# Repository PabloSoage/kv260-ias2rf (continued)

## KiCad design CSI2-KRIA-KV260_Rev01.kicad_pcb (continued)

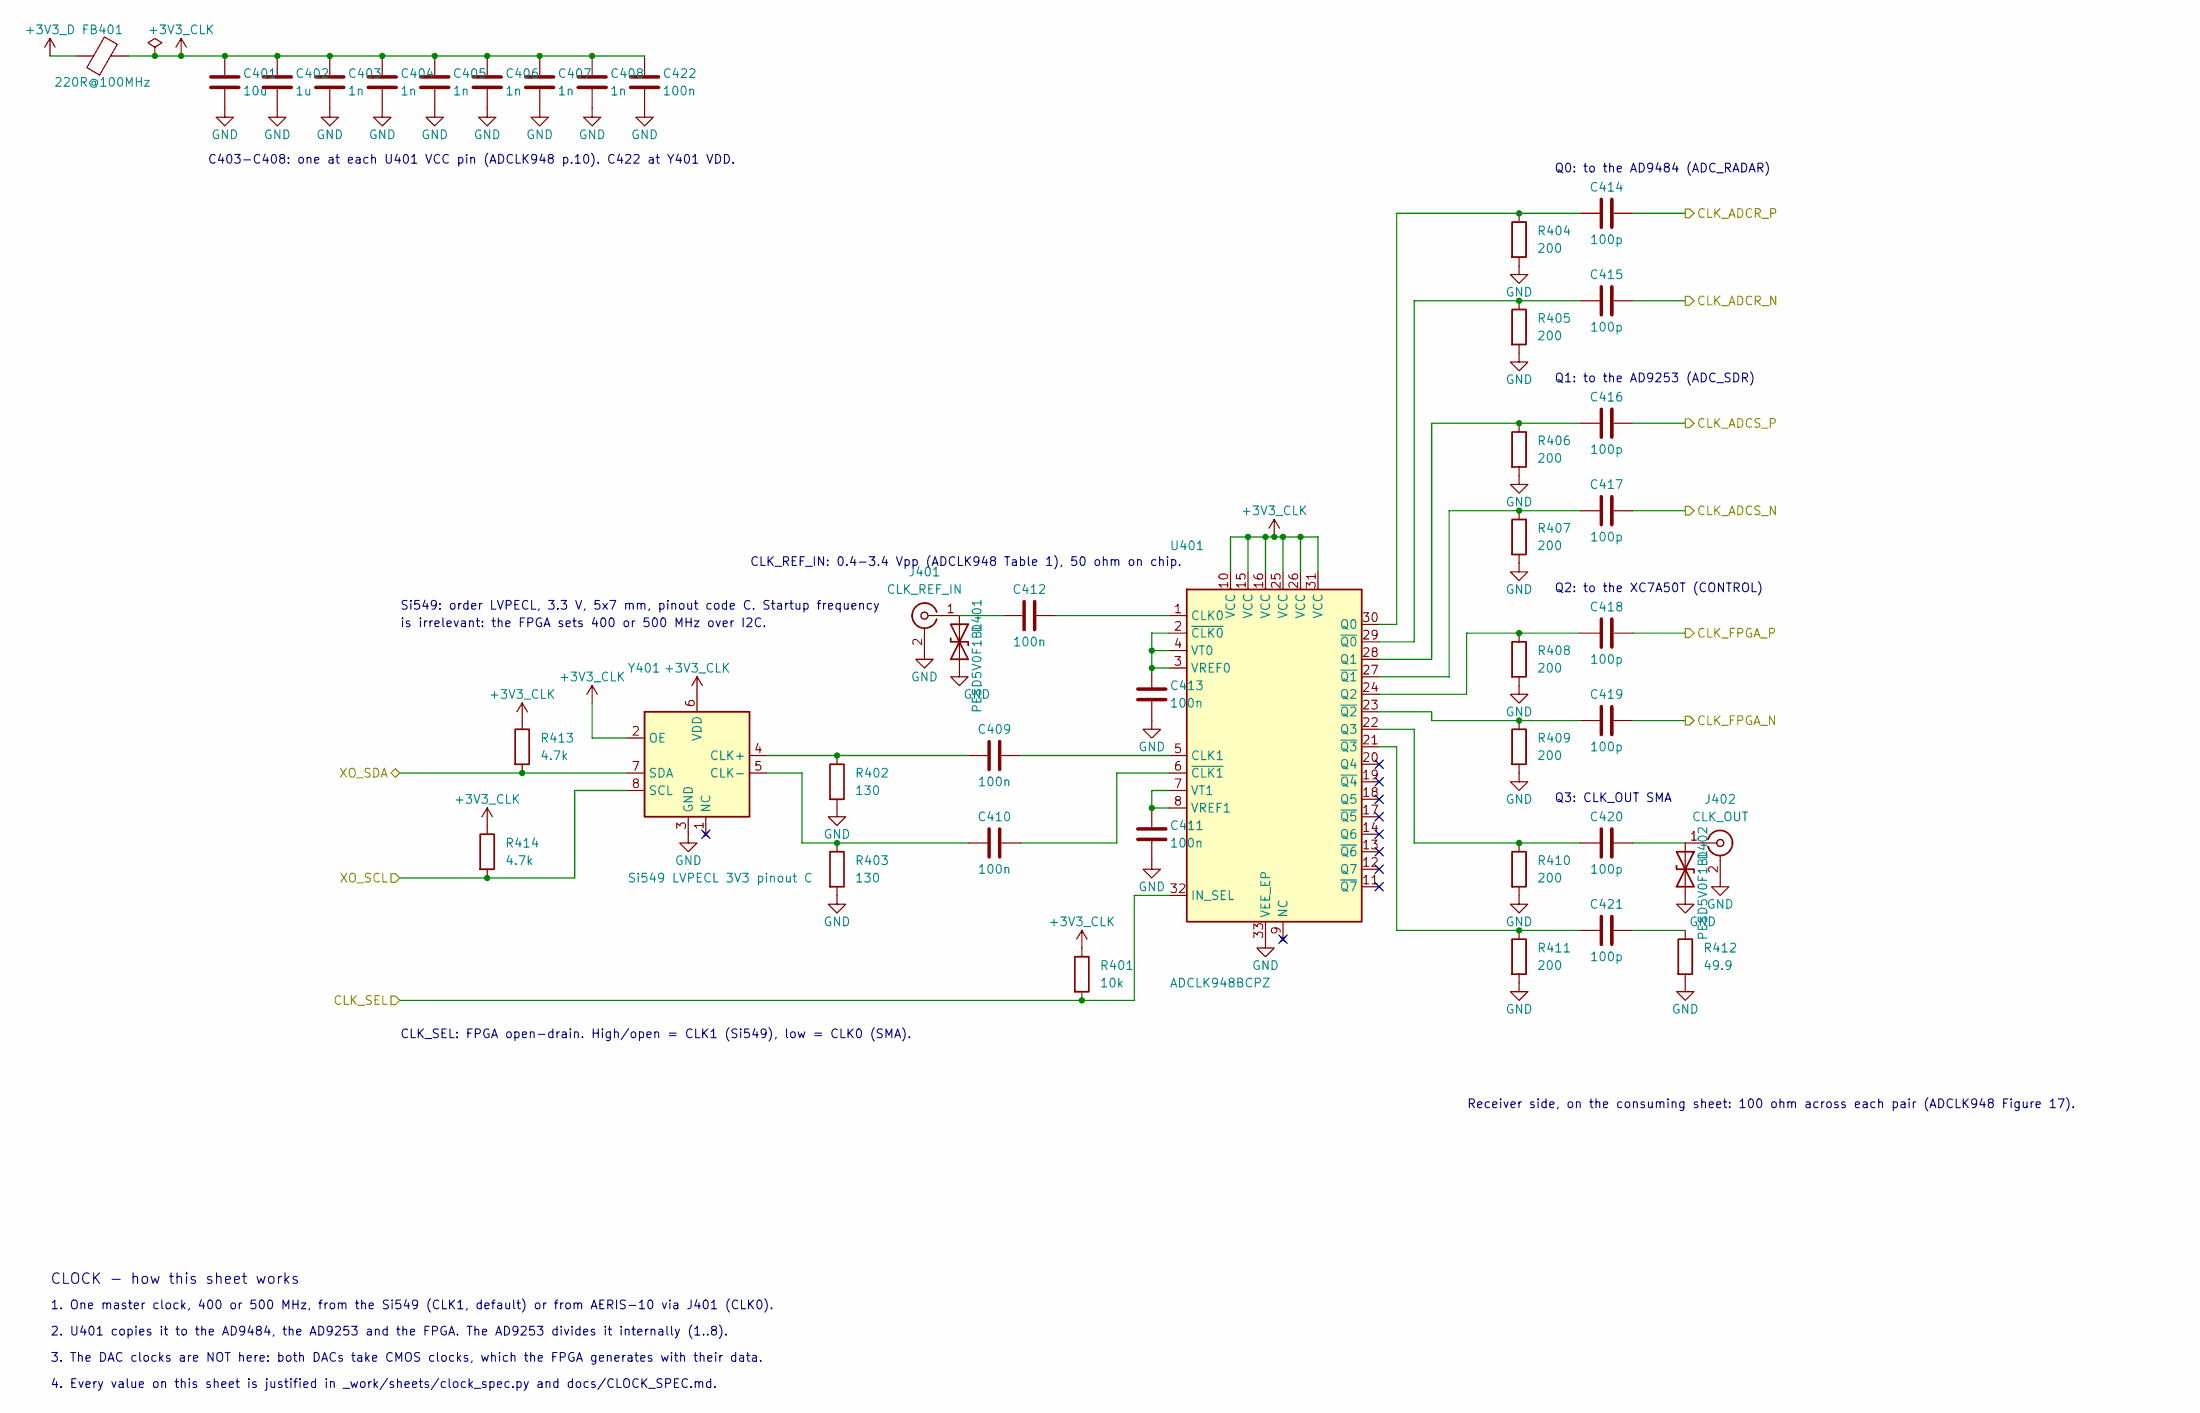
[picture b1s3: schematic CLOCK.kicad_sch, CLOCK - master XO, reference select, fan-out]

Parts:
C401: 10u; C_0805_2012Metric
C402: 1u; C_0402_1005Metric
C403, C404, C405, C406, C407, C408: 1n; C_0402_1005Metric
C409, C410, C411, C412, C413, C422: 100n; C_0402_1005Metric
C414, C415, C416, C417, C418, C419, C420, C421: 100p; C_0402_1005Metric
D401, D402: PESD5V0F1BL; D_SOD-882
FB401: 220R@100MHz; L_0603_1608Metric
J401: CLK_REF_IN; SMA_Samtec_SMA-J-P-H-ST-EM1_EdgeMount
J402: CLK_OUT; SMA_Samtec_SMA-J-P-H-ST-EM1_EdgeMount
R401: 10k; R_0402_1005Metric
R402, R403: 130; R_0402_1005Metric
R404, R405, R406, R407, R408, R409, R410, R411: 200; R_0402_1005Metric
R412: 49.9; R_0402_1005Metric
R413, R414: 4.7k; R_0402_1005Metric
U401: ADCLK948BCPZ; LFCSP-32-1EP_5x5mm_P0.5mm_EP2.7x2.7mm
Y401: Si549 LVPECL 3V3 pinout C; Oscillator_SMD_SI570_SI571_Standard

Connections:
+3V3_CLK: C401.1, C402.1, C403.1, C404.1, C405.1, C406.1, C407.1, C408.1, C422.1, FB401.2, R401.1, R413.1, R414.1, U401.10 (VCC), U401.15 (VCC), U401.16 (VCC), U401.25 (VCC), U401.26 (VCC), U401.31 (VCC), Y401.2 (OE), Y401.6 (VDD); also elsewhere on the board
+3V3_D: FB401.1; also elsewhere on the board
/CLK_ADCR_N: C415.2; also elsewhere on the board
/CLK_ADCR_P: C414.2; also elsewhere on the board
/CLK_ADCS_N: C417.2; also elsewhere on the board
/CLK_ADCS_P: C416.2; also elsewhere on the board
/CLK_FPGA_N: C419.2; also elsewhere on the board
/CLK_FPGA_P: C418.2; also elsewhere on the board
/CLK_SEL: R401.2, U401.32 (IN_SEL); also elsewhere on the board
/XO_SCL: R414.2, Y401.8 (SCL); also elsewhere on the board
/XO_SDA: R413.2, Y401.7 (SDA); also elsewhere on the board
GND: C401.2, C402.2, C403.2, C404.2, C405.2, C406.2, C407.2, C408.2, C411.2, C413.2, C422.2, D401.2 (A2), D402.2 (A2), J401.2 (Ext), J402.2 (Ext), R402.2, R403.2, R404.2, R405.2, R406.2, R407.2, R408.2, R409.2, R410.2, R411.2, R412.2, U401.33 (VEE_EP), Y401.3 (GND); also elsewhere on the board
unnamed: C421.2, R412.1
unnamed: C412.1, D401.1 (A1), J401.1 (In)
unnamed: C420.2, D402.1 (A1), J402.1 (In)
unnamed: C412.2, U401.1 (CLK0)
unnamed: C409.2, U401.5 (CLK1)
unnamed: C414.1, R404.1, U401.30 (Q0)
unnamed: C416.1, R406.1, U401.28 (Q1)
unnamed: C418.1, R408.1, U401.24 (Q2)
unnamed: C420.1, R410.1, U401.22 (Q3)
unnamed: C413.1, U401.2 (~CLK0), U401.3 (VREF0), U401.4 (VT0)
unnamed: C411.1, U401.7 (VT1), U401.8 (VREF1)
unnamed: C410.2, U401.6 (~CLK1)
unnamed: C415.1, R405.1, U401.29 (~Q0)
unnamed: C417.1, R407.1, U401.27 (~Q1)
unnamed: C419.1, R409.1, U401.23 (~Q2)
unnamed: C421.1, R411.1, U401.21 (~Q3)
unnamed: C409.1, R402.1, Y401.4 (CLK+)
unnamed: C410.1, R403.1, Y401.5 (CLK-)

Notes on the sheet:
C403-C408: one at each U401 VCC pin (ADCLK948 p.10). C422 at Y401 VDD.
CLK_REF_IN: 0.4-3.4 Vpp (ADCLK948 Table 1), 50 ohm on chip.
Si549: order LVPECL, 3.3 V, 5x7 mm, pinout code C. Startup frequency
is irrelevant: the FPGA sets 400 or 500 MHz over I2C.
CLK_SEL: FPGA open-drain. High/open = CLK1 (Si549), low = CLK0 (SMA).
Q0: to the AD9484 (ADC_RADAR)
Q1: to the AD9253 (ADC_SDR)
Q2: to the XC7A50T (CONTROL)
Q3: CLK_OUT SMA
Receiver side, on the consuming sheet: 100 ohm across each pair (ADCLK948 Figure 17).
CLOCK - how this sheet works
1. One master clock, 400 or 500 MHz, from the Si549 (CLK1, default) or from AERIS-10 via J401 (CLK0).
2. U401 copies it to the AD9484, the AD9253 and the FPGA. The AD9253 divides it internally (1..8).
3. The DAC clocks are NOT here: both DACs take CMOS clocks, which the FPGA generates with their data.
4. Every value on this sheet is justified in _work/sheets/clock_spec.py and docs/CLOCK_SPEC.md.

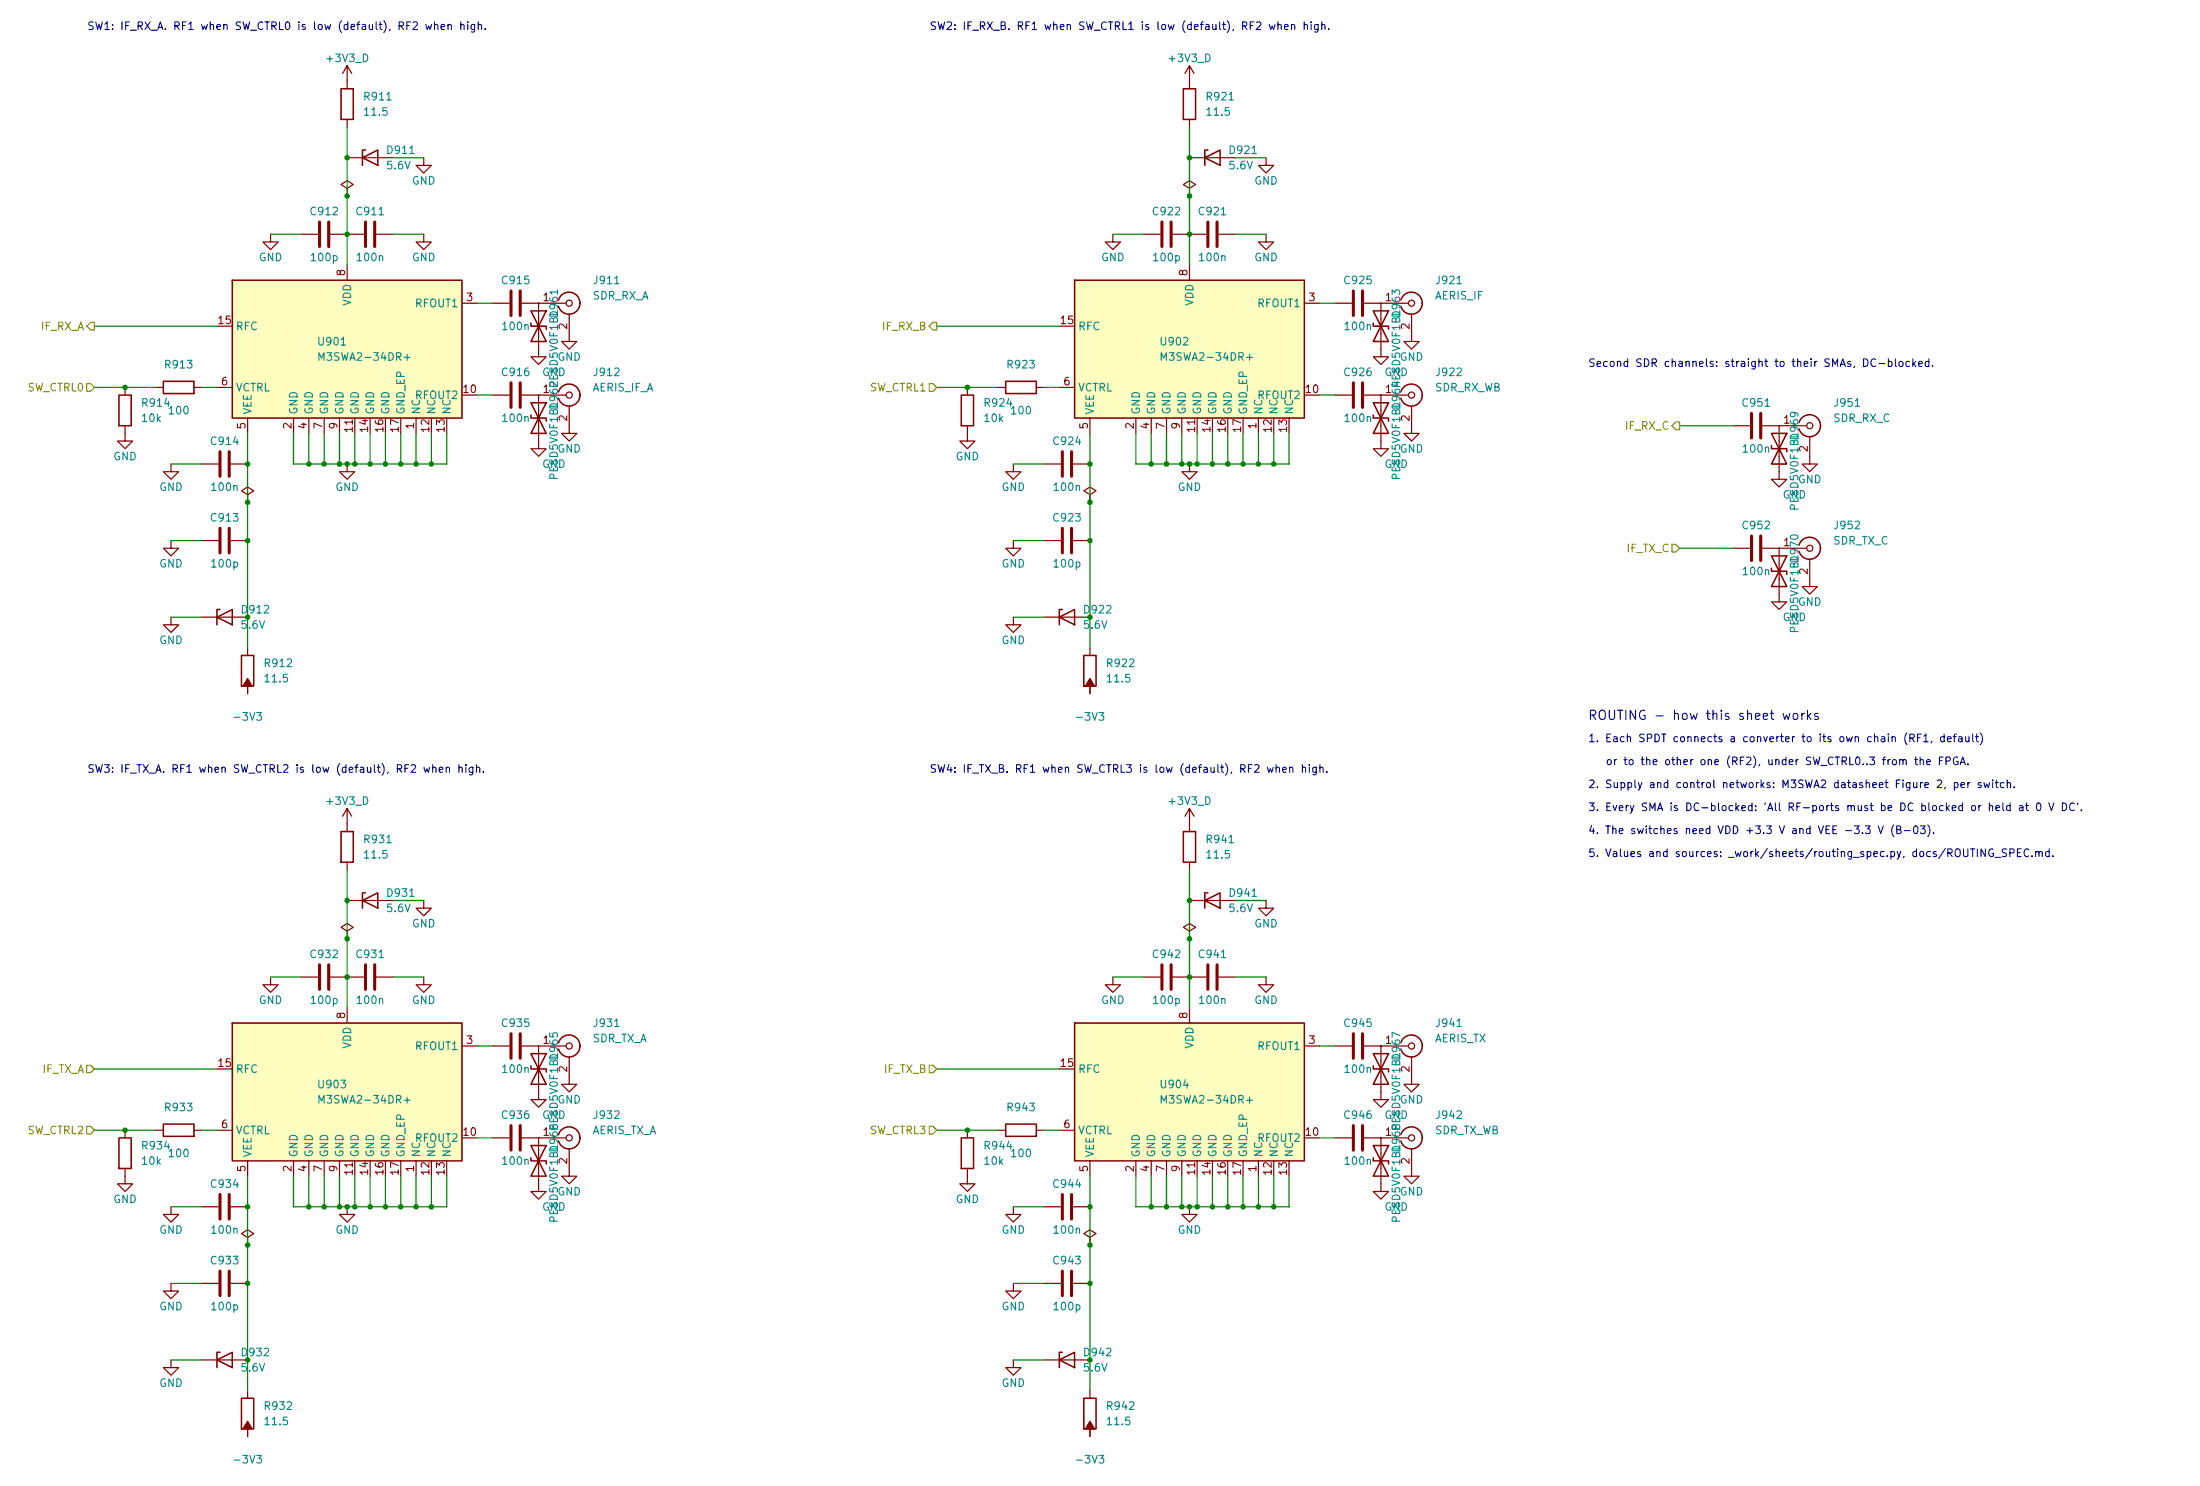
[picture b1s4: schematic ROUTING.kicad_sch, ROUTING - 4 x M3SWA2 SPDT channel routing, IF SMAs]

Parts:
C911, C914, C915, C916, C921, C924, C925, C926, C931, C934, C935, C936, C941, C944, C945, C946, C951, C952: 100n; C_0402_1005Metric
C912, C913, C922, C923, C932, C933, C942, C943: 100p; C_0402_1005Metric
D911, D912, D921, D922, D931, D932, D941, D942: 5.6V; D_SOD-123
D961, D962, D963, D964, D965, D966, D967, D968, D969, D970: PESD5V0F1BL; D_SOD-882
J911: SDR_RX_A; SMA_Samtec_SMA-J-P-H-ST-EM1_EdgeMount
J912: AERIS_IF_A; SMA_Samtec_SMA-J-P-H-ST-EM1_EdgeMount
J921: AERIS_IF; SMA_Samtec_SMA-J-P-H-ST-EM1_EdgeMount
J922: SDR_RX_WB; SMA_Samtec_SMA-J-P-H-ST-EM1_EdgeMount
J931: SDR_TX_A; SMA_Samtec_SMA-J-P-H-ST-EM1_EdgeMount
J932: AERIS_TX_A; SMA_Samtec_SMA-J-P-H-ST-EM1_EdgeMount
J941: AERIS_TX; SMA_Samtec_SMA-J-P-H-ST-EM1_EdgeMount
J942: SDR_TX_WB; SMA_Samtec_SMA-J-P-H-ST-EM1_EdgeMount
J951: SDR_RX_C; SMA_Samtec_SMA-J-P-H-ST-EM1_EdgeMount
J952: SDR_TX_C; SMA_Samtec_SMA-J-P-H-ST-EM1_EdgeMount
R911, R912, R921, R922, R931, R932, R941, R942: 11.5; R_0402_1005Metric
R913, R923, R933, R943: 100; R_0402_1005Metric
R914, R924, R934, R944: 10k; R_0402_1005Metric
U901, U902, U903, U904: M3SWA2-34DR+; MiniCircuits_DQ3005

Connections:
+3V3_D: R911.1, R921.1, R931.1, R941.1; also elsewhere on the board
-3V3: R912.2, R922.2, R932.2, R942.2; also elsewhere on the board
/IF_RX_A: U901.15 (RFC); also elsewhere on the board
/IF_RX_B: U902.15 (RFC); also elsewhere on the board
/IF_RX_C: C951.1; also elsewhere on the board
/IF_TX_A: U903.15 (RFC); also elsewhere on the board
/IF_TX_B: U904.15 (RFC); also elsewhere on the board
/IF_TX_C: C952.1; also elsewhere on the board
/SW_CTRL0: R913.1, R914.1; also elsewhere on the board
/SW_CTRL1: R923.1, R924.1; also elsewhere on the board
/SW_CTRL2: R933.1, R934.1; also elsewhere on the board
/SW_CTRL3: R943.1, R944.1; also elsewhere on the board
GND: C911.2, C912.2, C913.1, C914.1, C921.2, C922.2, C923.1, C924.1, C931.2, C932.2, C933.1, C934.1, C941.2, C942.2, C943.1, C944.1, D911.2 (A), D912.1 (K), D921.2 (A), D922.1 (K), D931.2 (A), D932.1 (K), D941.2 (A), D942.1 (K), D961.2 (A2), D962.2 (A2), D963.2 (A2), D964.2 (A2), D965.2 (A2), D966.2 (A2), D967.2 (A2), D968.2 (A2), D969.2 (A2), D970.2 (A2), J911.2 (Ext), J912.2 (Ext), J921.2 (Ext), J922.2 (Ext), J931.2 (Ext), J932.2 (Ext), J941.2 (Ext), J942.2 (Ext), J951.2 (Ext), J952.2 (Ext), R914.2, R924.2, R934.2, R944.2, U901.1 (NC), U901.2 (GND), U901.4 (GND), U901.7 (GND), U901.9 (GND), U901.11 (GND), U901.12 (NC), U901.13 (NC), U901.14 (GND), U901.16 (GND), U901.17 (GND_EP), U902.1 (NC), U902.2 (GND), U902.4 (GND), U902.7 (GND), U902.9 (GND), U902.11 (GND), U902.12 (NC), U902.13 (NC), U902.14 (GND), U902.16 (GND), U902.17 (GND_EP), U903.1 (NC), U903.2 (GND), U903.4 (GND), U903.7 (GND), U903.9 (GND), U903.11 (GND), U903.12 (NC), U903.13 (NC), U903.14 (GND), U903.16 (GND), U903.17 (GND_EP), U904.1 (NC), U904.2 (GND), U904.4 (GND), U904.7 (GND), U904.9 (GND), U904.11 (GND), U904.12 (NC), U904.13 (NC), U904.14 (GND), U904.16 (GND), U904.17 (GND_EP); also elsewhere on the board
unnamed: C911.1, C912.1, D911.1 (K), R911.2, U901.8 (VDD)
unnamed: C913.2, C914.2, D912.2 (A), R912.1, U901.5 (VEE)
unnamed: C921.1, C922.1, D921.1 (K), R921.2, U902.8 (VDD)
unnamed: C923.2, C924.2, D922.2 (A), R922.1, U902.5 (VEE)
unnamed: C931.1, C932.1, D931.1 (K), R931.2, U903.8 (VDD)
unnamed: C933.2, C934.2, D932.2 (A), R932.1, U903.5 (VEE)
unnamed: C941.1, C942.1, D941.1 (K), R941.2, U904.8 (VDD)
unnamed: C943.2, C944.2, D942.2 (A), R942.1, U904.5 (VEE)
unnamed: C915.2, D961.1 (A1), J911.1 (In)
unnamed: C916.2, D962.1 (A1), J912.1 (In)
unnamed: C925.2, D963.1 (A1), J921.1 (In)
unnamed: C926.2, D964.1 (A1), J922.1 (In)
unnamed: C935.2, D965.1 (A1), J931.1 (In)
unnamed: C936.2, D966.1 (A1), J932.1 (In)
unnamed: C945.2, D967.1 (A1), J941.1 (In)
unnamed: C946.2, D968.1 (A1), J942.1 (In)
unnamed: C951.2, D969.1 (A1), J951.1 (In)
unnamed: C952.2, D970.1 (A1), J952.1 (In)
unnamed: C915.1, U901.3 (RFOUT1)
unnamed: C916.1, U901.10 (RFOUT2)
unnamed: R913.2, U901.6 (VCTRL)
unnamed: C925.1, U902.3 (RFOUT1)
unnamed: C926.1, U902.10 (RFOUT2)
unnamed: R923.2, U902.6 (VCTRL)
unnamed: C935.1, U903.3 (RFOUT1)
unnamed: C936.1, U903.10 (RFOUT2)
unnamed: R933.2, U903.6 (VCTRL)
unnamed: C945.1, U904.3 (RFOUT1)
unnamed: C946.1, U904.10 (RFOUT2)
unnamed: R943.2, U904.6 (VCTRL)

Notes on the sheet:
SW1: IF_RX_A. RF1 when SW_CTRL0 is low (default), RF2 when high.
SW2: IF_RX_B. RF1 when SW_CTRL1 is low (default), RF2 when high.
SW3: IF_TX_A. RF1 when SW_CTRL2 is low (default), RF2 when high.
SW4: IF_TX_B. RF1 when SW_CTRL3 is low (default), RF2 when high.
Second SDR channels: straight to their SMAs, DC-blocked.
ROUTING - how this sheet works
1. Each SPDT connects a converter to its own chain (RF1, default)
or to the other one (RF2), under SW_CTRL0..3 from the FPGA.
2. Supply and control networks: M3SWA2 datasheet Figure 2, per switch.
3. Every SMA is DC-blocked: 'All RF-ports must be DC blocked or held at 0 V DC'.
4. The switches need VDD +3.3 V and VEE -3.3 V (B-03).
5. Values and sources: _work/sheets/routing_spec.py, docs/ROUTING_SPEC.md.

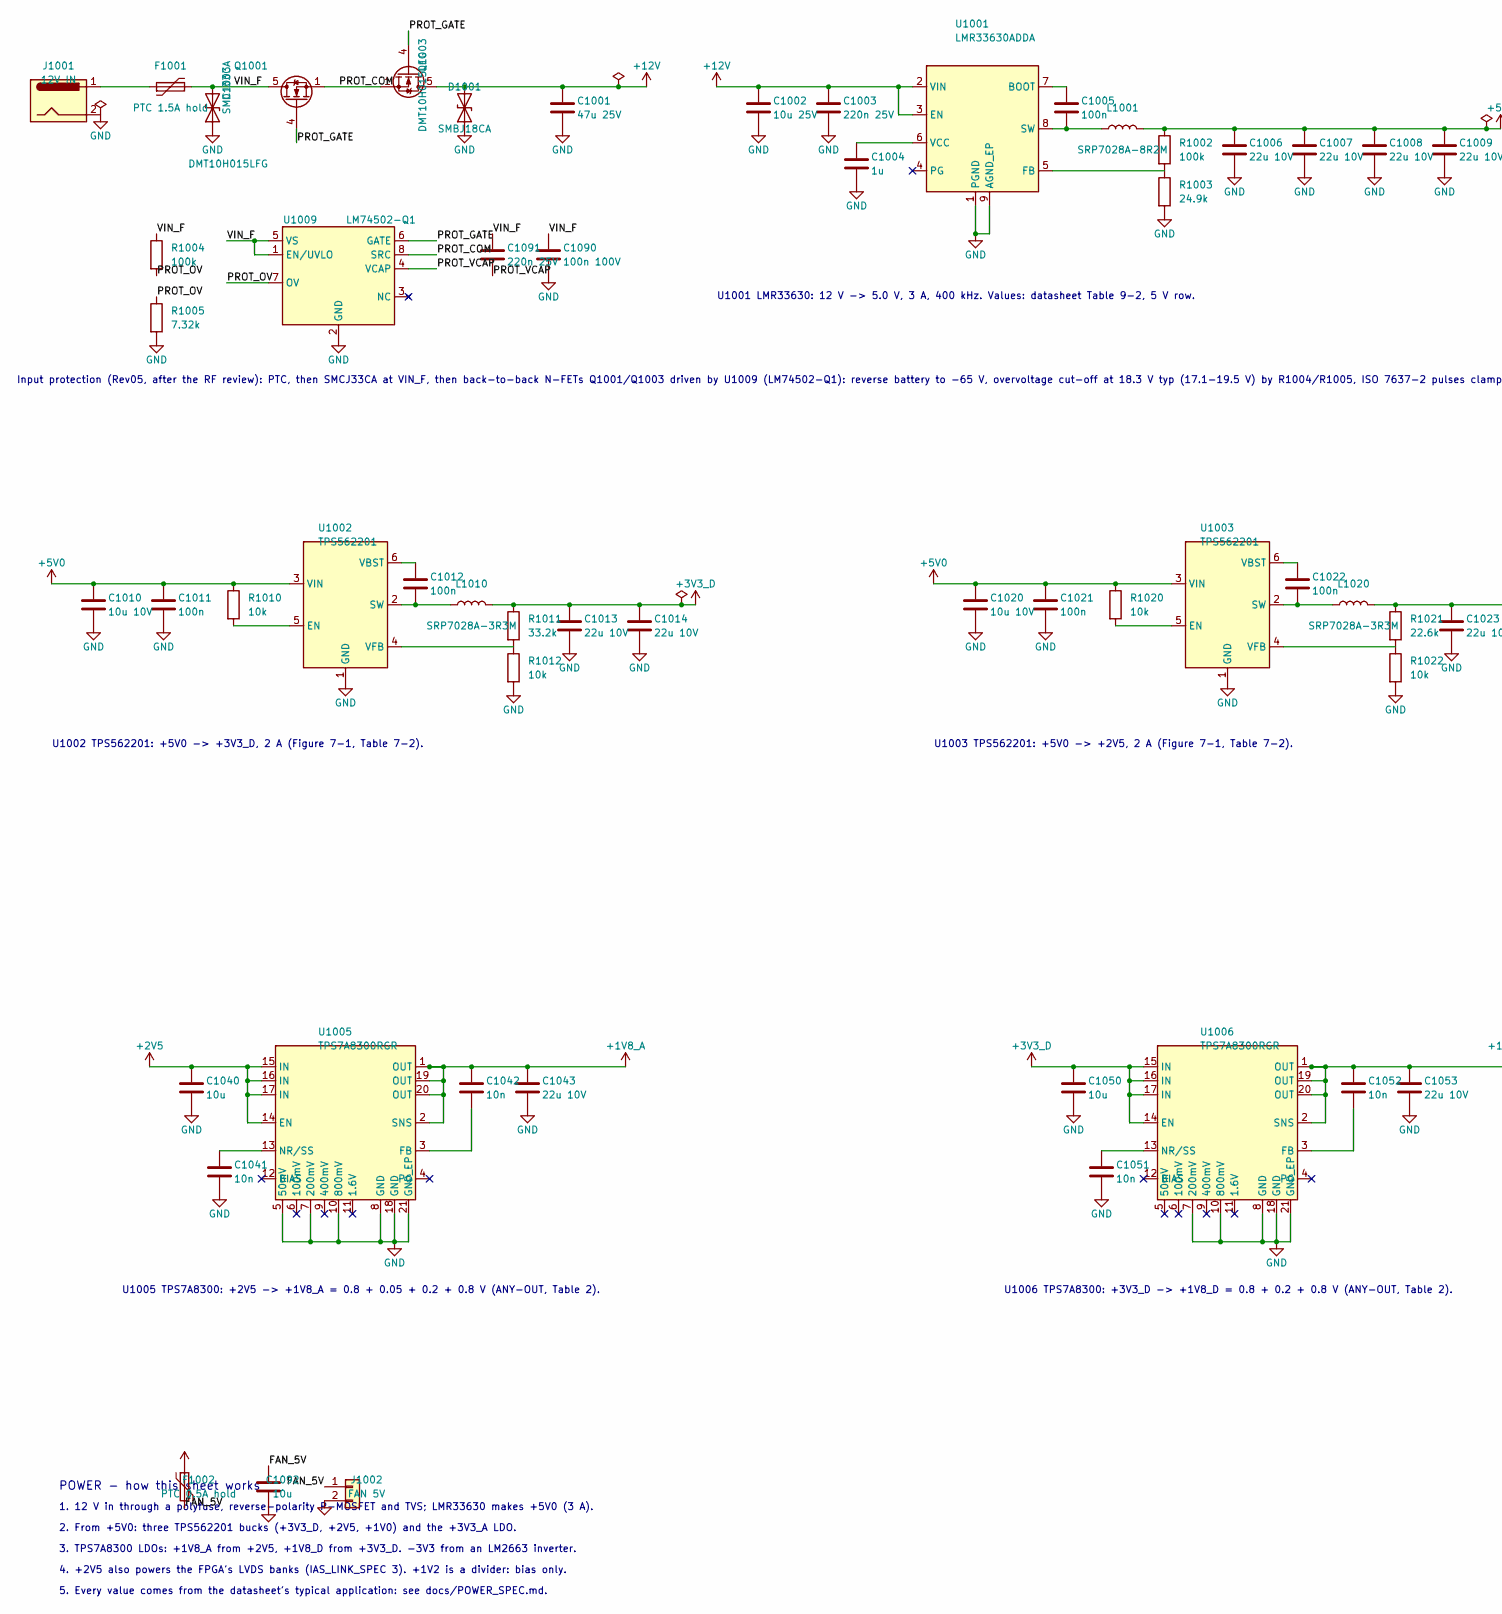
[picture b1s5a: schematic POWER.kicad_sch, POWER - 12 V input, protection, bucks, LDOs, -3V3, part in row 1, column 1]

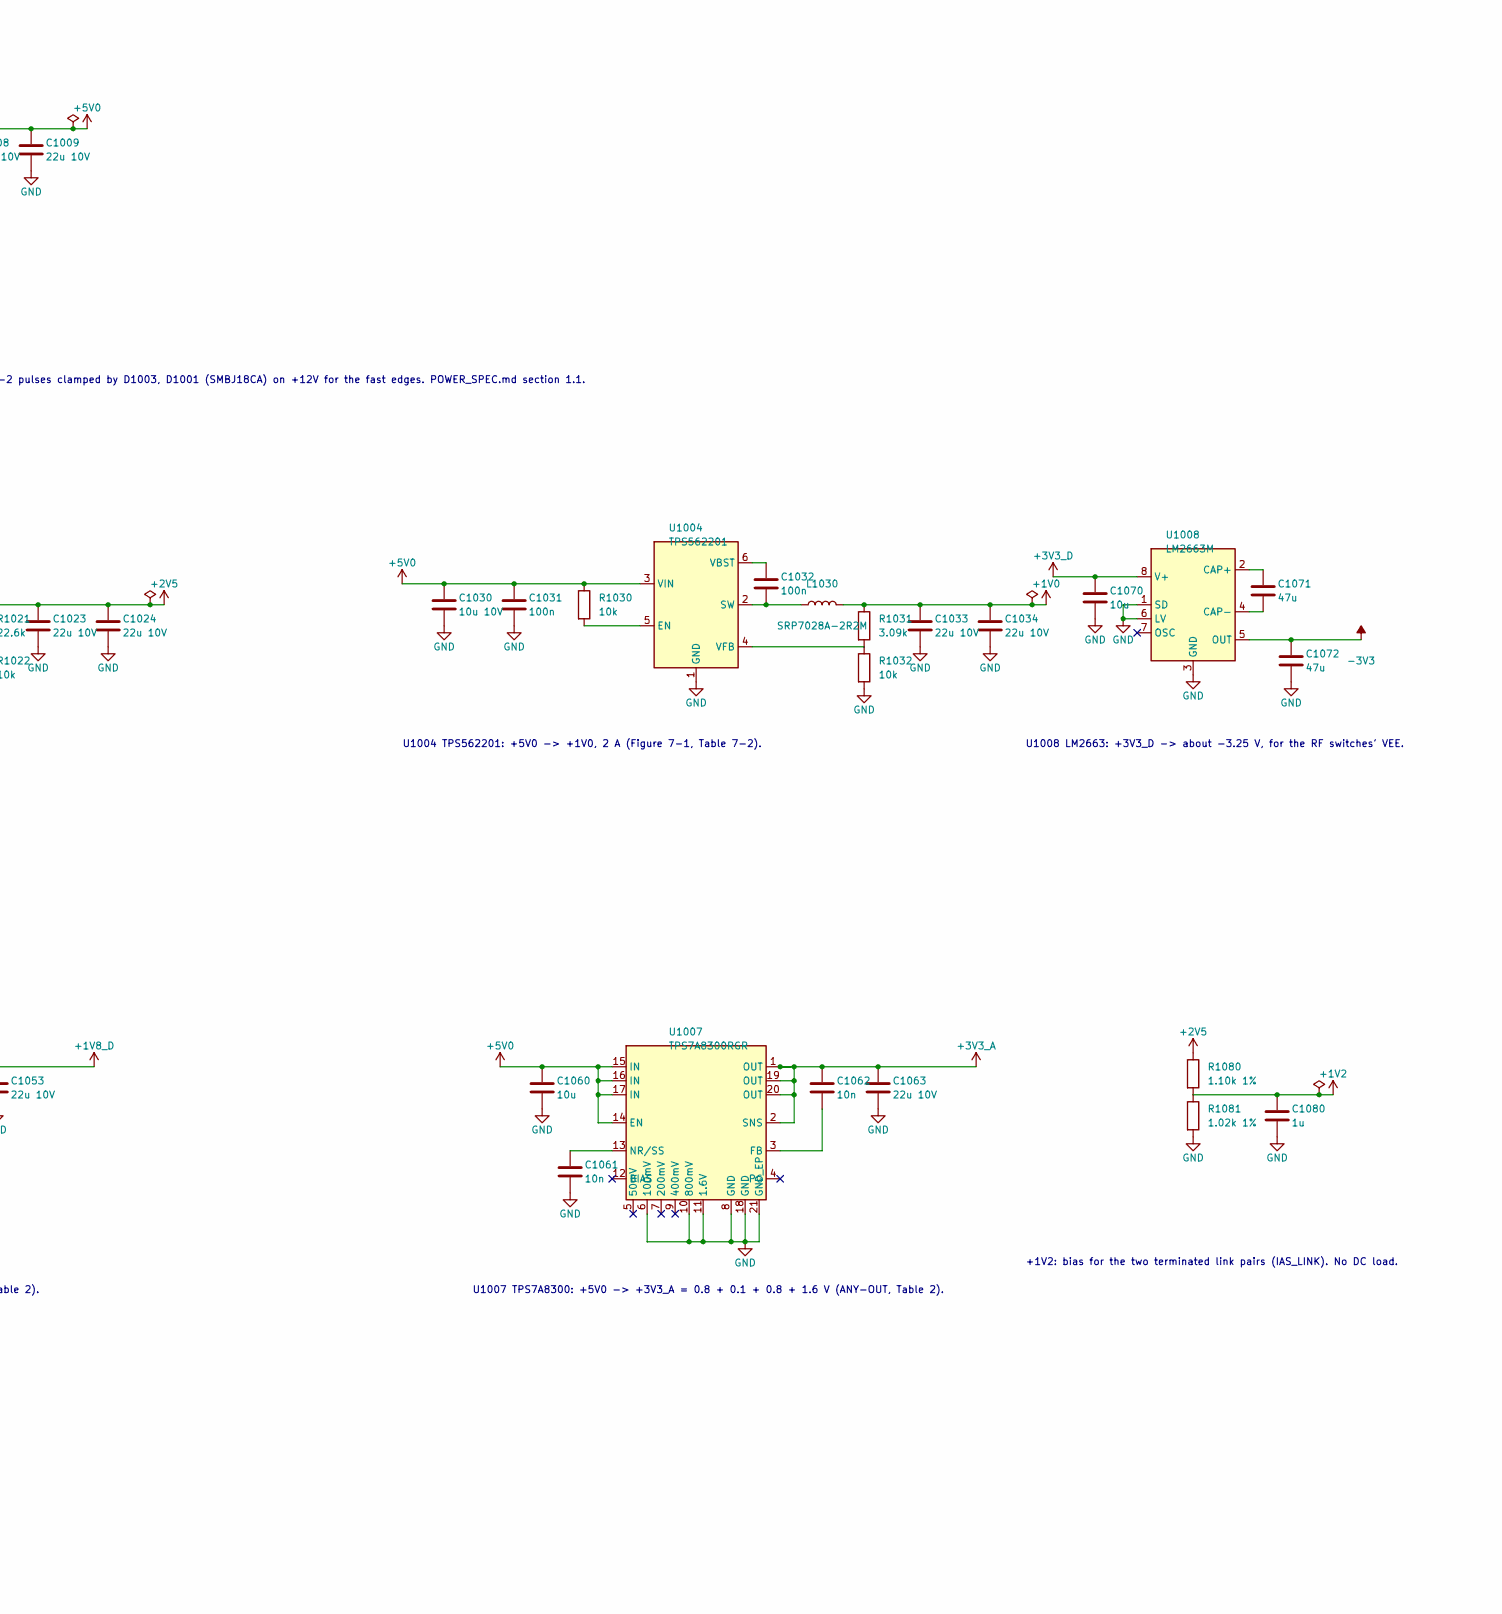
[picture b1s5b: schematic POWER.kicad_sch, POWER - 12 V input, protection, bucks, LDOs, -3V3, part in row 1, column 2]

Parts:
C1001: 47u 25V; C_1210_3225Metric
C1002: 10u 25V; C_1206_3216Metric
C1003, C1091: 220n 25V; C_0603_1608Metric
C1004, C1080: 1u; C_0402_1005Metric
C1005, C1011, C1012, C1021, C1022, C1031, C1032: 100n; C_0402_1005Metric
C1006, C1007, C1008, C1009, C1013, C1014, C1023, C1024, C1033, C1034, C1043, C1053, C1063: 22u 10V; C_0805_2012Metric
C1010, C1020, C1030: 10u 10V; C_0805_2012Metric
C1040, C1050, C1060, C1070, C1092: 10u; C_0805_2012Metric
C1041, C1042, C1051, C1052, C1061, C1062: 10n; C_0402_1005Metric
C1071, C1072: 47u; C_1206_3216Metric
C1090: 100n 100V; C_0603_1608Metric
D1001: SMBJ18CA; D_SMB
D1003: SMCJ33CA; D_SMC
F1001: PTC 1.5A hold; Fuse_1812_4532Metric
F1002: PTC 0.5A hold; Fuse_1206_3216Metric
J1001: 12V IN; BarrelJack_CUI_PJ-102AH_Horizontal
J1002: FAN 5V; JST_PH_B2B-PH-K_1x02_P2.00mm_Vertical
L1001: SRP7028A-8R2M; L_Bourns_SRP7028A_7.3x6.6mm
L1010, L1020: SRP7028A-3R3M; L_Bourns_SRP7028A_7.3x6.6mm
L1030: SRP7028A-2R2M; L_Bourns_SRP7028A_7.3x6.6mm
Q1001, Q1003: DMT10H015LFG; Diodes_PowerDI3333-8
R1002: 100k; R_0402_1005Metric
R1003: 24.9k; R_0402_1005Metric
R1004: 100k; R_0603_1608Metric
R1005: 7.32k; R_0603_1608Metric
R1010, R1012, R1020, R1022, R1030, R1032: 10k; R_0402_1005Metric
R1011: 33.2k; R_0402_1005Metric
R1021: 22.6k; R_0402_1005Metric
R1031: 3.09k; R_0402_1005Metric
R1080: 1.10k 1%; R_0402_1005Metric
R1081: 1.02k 1%; R_0402_1005Metric
U1001: LMR33630ADDA; Texas_HSOP-8-1EP_3.9x4.9mm_P1.27mm
U1002, U1003, U1004: TPS562201; SOT-23-6
U1005, U1006, U1007: TPS7A8300RGR; QFN-20-1EP_3.5x3.5mm_P0.5mm_EP2x2mm
U1008: LM2663M; SOIC-8_3.9x4.9mm_P1.27mm
U1009: LM74502-Q1; SOT-23-8

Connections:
+1V0: C1033.1, C1034.1, L1030.2, R1031.1; also elsewhere on the board
+1V2: C1080.1, R1080.2, R1081.1; also elsewhere on the board
+1V8_A: C1042.1, C1043.1, U1005.1 (OUT), U1005.2 (SNS), U1005.19 (OUT), U1005.20 (OUT); also elsewhere on the board
+1V8_D: C1052.1, C1053.1, U1006.1 (OUT), U1006.2 (SNS), U1006.19 (OUT), U1006.20 (OUT); also elsewhere on the board
+2V5: C1023.1, C1024.1, C1040.1, L1020.2, R1021.1, R1080.1, U1005.14 (EN), U1005.15 (IN), U1005.16 (IN), U1005.17 (IN); also elsewhere on the board
+3V3_A: C1062.1, C1063.1, U1007.1 (OUT), U1007.2 (SNS), U1007.19 (OUT), U1007.20 (OUT); also elsewhere on the board
+3V3_D: C1013.1, C1014.1, C1050.1, C1070.1, L1010.2, R1011.1, U1006.14 (EN), U1006.15 (IN), U1006.16 (IN), U1006.17 (IN), U1008.8 (V+); also elsewhere on the board
+5V0: C1006.1, C1007.1, C1008.1, C1009.1, C1010.1, C1011.1, C1020.1, C1021.1, C1030.1, C1031.1, C1060.1, F1002.1, L1001.2, R1002.1, R1010.1, R1020.1, R1030.1, U1002.3 (VIN), U1003.3 (VIN), U1004.3 (VIN), U1007.14 (EN), U1007.15 (IN), U1007.16 (IN), U1007.17 (IN); also elsewhere on the board
+12V: C1001.1, C1002.1, C1003.1, D1001.2 (A2), Q1003.5 (D), U1001.2 (VIN), U1001.3 (EN)
-3V3: C1072.1, U1008.5 (OUT); also elsewhere on the board
/POWER/FAN_5V: C1092.1, F1002.2, J1002.1
/POWER/PROT_COM: Q1001.1 (S), Q1001.2 (S), Q1001.3 (S), Q1003.1 (S), Q1003.2 (S), Q1003.3 (S), U1009.8 (SRC)
/POWER/PROT_GATE: Q1001.4 (G), Q1003.4 (G), U1009.6 (GATE)
/POWER/PROT_OV: R1004.2, R1005.1, U1009.7 (OV)
/POWER/PROT_VCAP: C1091.2, U1009.4 (VCAP)
/POWER/VIN_F: C1090.1, C1091.1, D1003.2 (A2), F1001.2, Q1001.5 (D), R1004.1, U1009.1 (EN/UVLO), U1009.5 (VS)
GND: C1001.2, C1002.2, C1003.2, C1004.2, C1006.2, C1007.2, C1008.2, C1009.2, C1010.2, C1011.2, C1013.2, C1014.2, C1020.2, C1021.2, C1023.2, C1024.2, C1030.2, C1031.2, C1033.2, C1034.2, C1040.2, C1041.2, C1043.2, C1050.2, C1051.2, C1053.2, C1060.2, C1061.2, C1063.2, C1070.2, C1072.2, C1080.2, C1090.2, C1092.2, D1001.1 (A1), D1003.1 (A1), J1001.2, J1002.2, R1003.2, R1005.2, R1012.2, R1022.2, R1032.2, R1081.2, U1001.1 (PGND), U1001.9 (AGND_EP), U1002.1 (GND), U1003.1 (GND), U1004.1 (GND), U1005.5 (50mV), U1005.7 (200mV), U1005.8 (GND), U1005.10 (800mV), U1005.18 (GND), U1005.21 (GND_EP), U1006.7 (200mV), U1006.8 (GND), U1006.10 (800mV), U1006.18 (GND), U1006.21 (GND_EP), U1007.6 (100mV), U1007.8 (GND), U1007.10 (800mV), U1007.11 (1.6V), U1007.18 (GND), U1007.21 (GND_EP), U1008.1 (SD), U1008.3 (GND), U1008.6 (LV), U1009.2 (GND); also elsewhere on the board
unnamed: F1001.1, J1001.1
unnamed: C1005.1, U1001.7 (BOOT)
unnamed: R1002.2, R1003.1, U1001.5 (FB)
unnamed: C1005.2, L1001.1, U1001.8 (SW)
unnamed: C1004.1, U1001.6 (VCC)
unnamed: R1010.2, U1002.5 (EN)
unnamed: C1012.2, L1010.1, U1002.2 (SW)
unnamed: C1012.1, U1002.6 (VBST)
unnamed: R1011.2, R1012.1, U1002.4 (VFB)
unnamed: R1020.2, U1003.5 (EN)
unnamed: C1022.2, L1020.1, U1003.2 (SW)
unnamed: C1022.1, U1003.6 (VBST)
unnamed: R1021.2, R1022.1, U1003.4 (VFB)
unnamed: R1030.2, U1004.5 (EN)
unnamed: C1032.2, L1030.1, U1004.2 (SW)
unnamed: C1032.1, U1004.6 (VBST)
unnamed: R1031.2, R1032.1, U1004.4 (VFB)
unnamed: C1042.2, U1005.3 (FB)
unnamed: C1041.1, U1005.13 (NR/SS)
unnamed: C1052.2, U1006.3 (FB)
unnamed: C1051.1, U1006.13 (NR/SS)
unnamed: C1062.2, U1007.3 (FB)
unnamed: C1061.1, U1007.13 (NR/SS)
unnamed: C1071.1, U1008.2 (CAP+)
unnamed: C1071.2, U1008.4 (CAP-)

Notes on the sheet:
U1001 LMR33630: 12 V -> 5.0 V, 3 A, 400 kHz. Values: datasheet Table 9-2, 5 V row.
U1002 TPS562201: +5V0 -> +3V3_D, 2 A (Figure 7-1, Table 7-2).
U1003 TPS562201: +5V0 -> +2V5, 2 A (Figure 7-1, Table 7-2).
U1004 TPS562201: +5V0 -> +1V0, 2 A (Figure 7-1, Table 7-2).
U1005 TPS7A8300: +2V5 -> +1V8_A = 0.8 + 0.05 + 0.2 + 0.8 V (ANY-OUT, Table 2).
U1006 TPS7A8300: +3V3_D -> +1V8_D = 0.8 + 0.2 + 0.8 V (ANY-OUT, Table 2).
U1007 TPS7A8300: +5V0 -> +3V3_A = 0.8 + 0.1 + 0.8 + 1.6 V (ANY-OUT, Table 2).
U1008 LM2663: +3V3_D -> about -3.25 V, for the RF switches' VEE.
+1V2: bias for the two terminated link pairs (IAS_LINK). No DC load.
POWER - how this sheet works
1. 12 V in through a polyfuse, reverse-polarity P-MOSFET and TVS; LMR33630 makes +5V0 (3 A).
2. From +5V0: three TPS562201 bucks (+3V3_D, +2V5, +1V0) and the +3V3_A LDO.
3. TPS7A8300 LDOs: +1V8_A from +2V5, +1V8_D from +3V3_D. -3V3 from an LM2663 inverter.
4. +2V5 also powers the FPGA's LVDS banks (IAS_LINK_SPEC 3). +1V2 is a divider: bias only.
5. Every value comes from the datasheet's typical application: see docs/POWER_SPEC.md.
Input protection (Rev05, after the RF review): PTC, then SMCJ33CA at VIN_F, then back-to-back N-FETs Q1001/Q1003 driven by U1009 (LM74502-Q1): reverse battery to -65 V, overvoltage cut-off at 18.3 V typ (17.1-19.5 V) by R1004/R1005, ISO 7637-2 pulses clamped by D1003, D1001 (SMBJ18CA) on +12V for t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
